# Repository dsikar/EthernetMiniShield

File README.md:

# EthernetMiniShield

Ethernet connector for the Arduino CNC Shield.

## Schematic

## Board

## BOM

For boards placed on CNC shield:

1. [RJ45 8-Pin Connector] x1 http://bit.ly/2og5aNq 
2. [2.45mm female pin header](http://ebay.eu/2oAhZgO) - 4 pins x2 rows
3. Molex KK 0.1" PCB header 2-way x1
4. Molex KK 0.1" PCB housing 2-way x1
5. Molex KK 0.1" PCB contacts x2
6. Wires (GND, signal) TBD
7. Housing TBD
8. Contacts TBD

For boards placed on pump:

1. [RJ45 8-Pin Connector] x1 http://bit.ly/2og5aNq 
2. Molex KK 0.1" PCB header 4-way x1 (Stepper)
3. Molex KK 0.1" PCB header 2-way x1
4. Molex KK 0.1" PCB housing 2-way x1
5. Molex KK 0.1" PCB contacts x2
6. Wires (GND, signal) TBD
7. Housing TBD
8. Contacts TBD

## Supplier

PCBWay.com - compress and upload all files in eagle directory except .sch, .brd and cam sub-directory.

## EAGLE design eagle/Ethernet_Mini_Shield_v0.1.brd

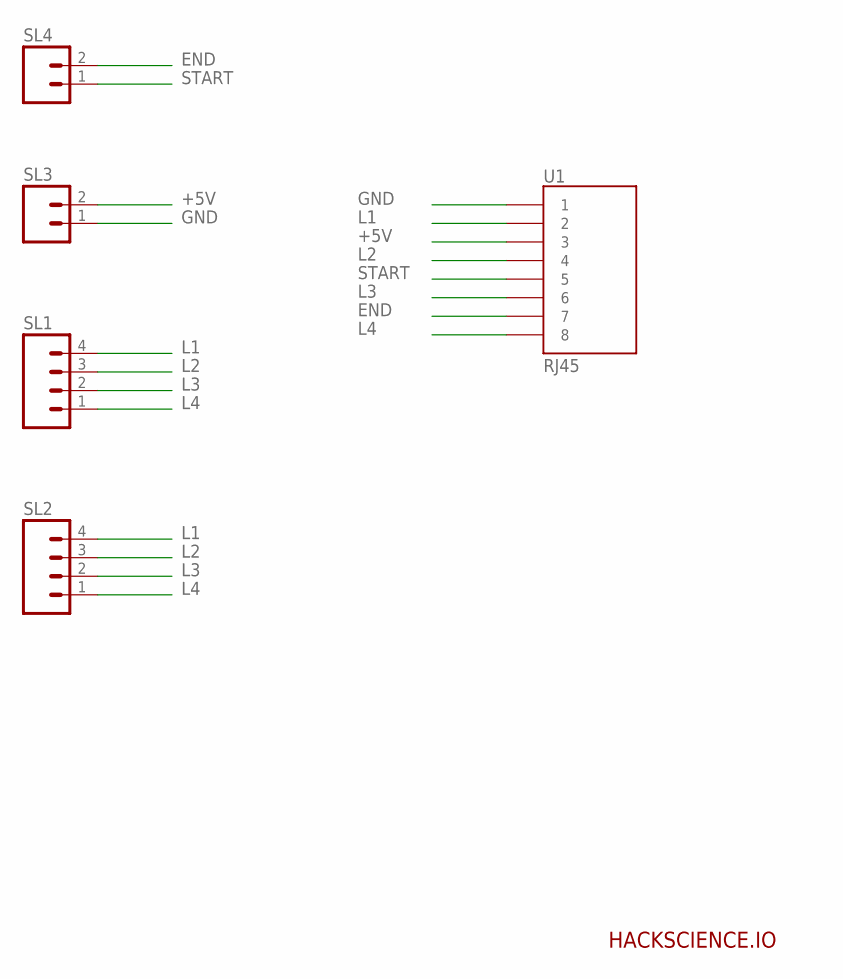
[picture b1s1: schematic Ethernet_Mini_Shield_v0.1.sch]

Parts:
SL1, SL2: M04; 04P
SL3, SL4: M02; 02P
U1: RJ45; RJ45-8

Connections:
+5V: SL3.2, U1.3
END: SL4.2, U1.7
GND: SL3.1, U1.1
L1: SL1.4, SL2.4, U1.2
L2: SL1.3, SL2.3, U1.4
L3: SL1.2, SL2.2, U1.6
L4: SL1.1, SL2.1, U1.8
START: SL4.1, U1.5

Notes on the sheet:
HACKSCIENCE.IO

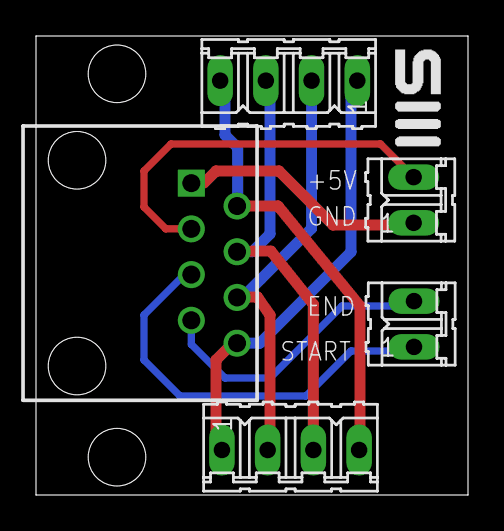
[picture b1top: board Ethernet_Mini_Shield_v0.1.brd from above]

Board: 2 copper layers, 24.0 x 25.5 mm, 5 parts (0 on the bottom side), 8 nets.

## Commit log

2017-04-23 First commit. Moved from public repo.
2017-05-21 Added version 0.2
